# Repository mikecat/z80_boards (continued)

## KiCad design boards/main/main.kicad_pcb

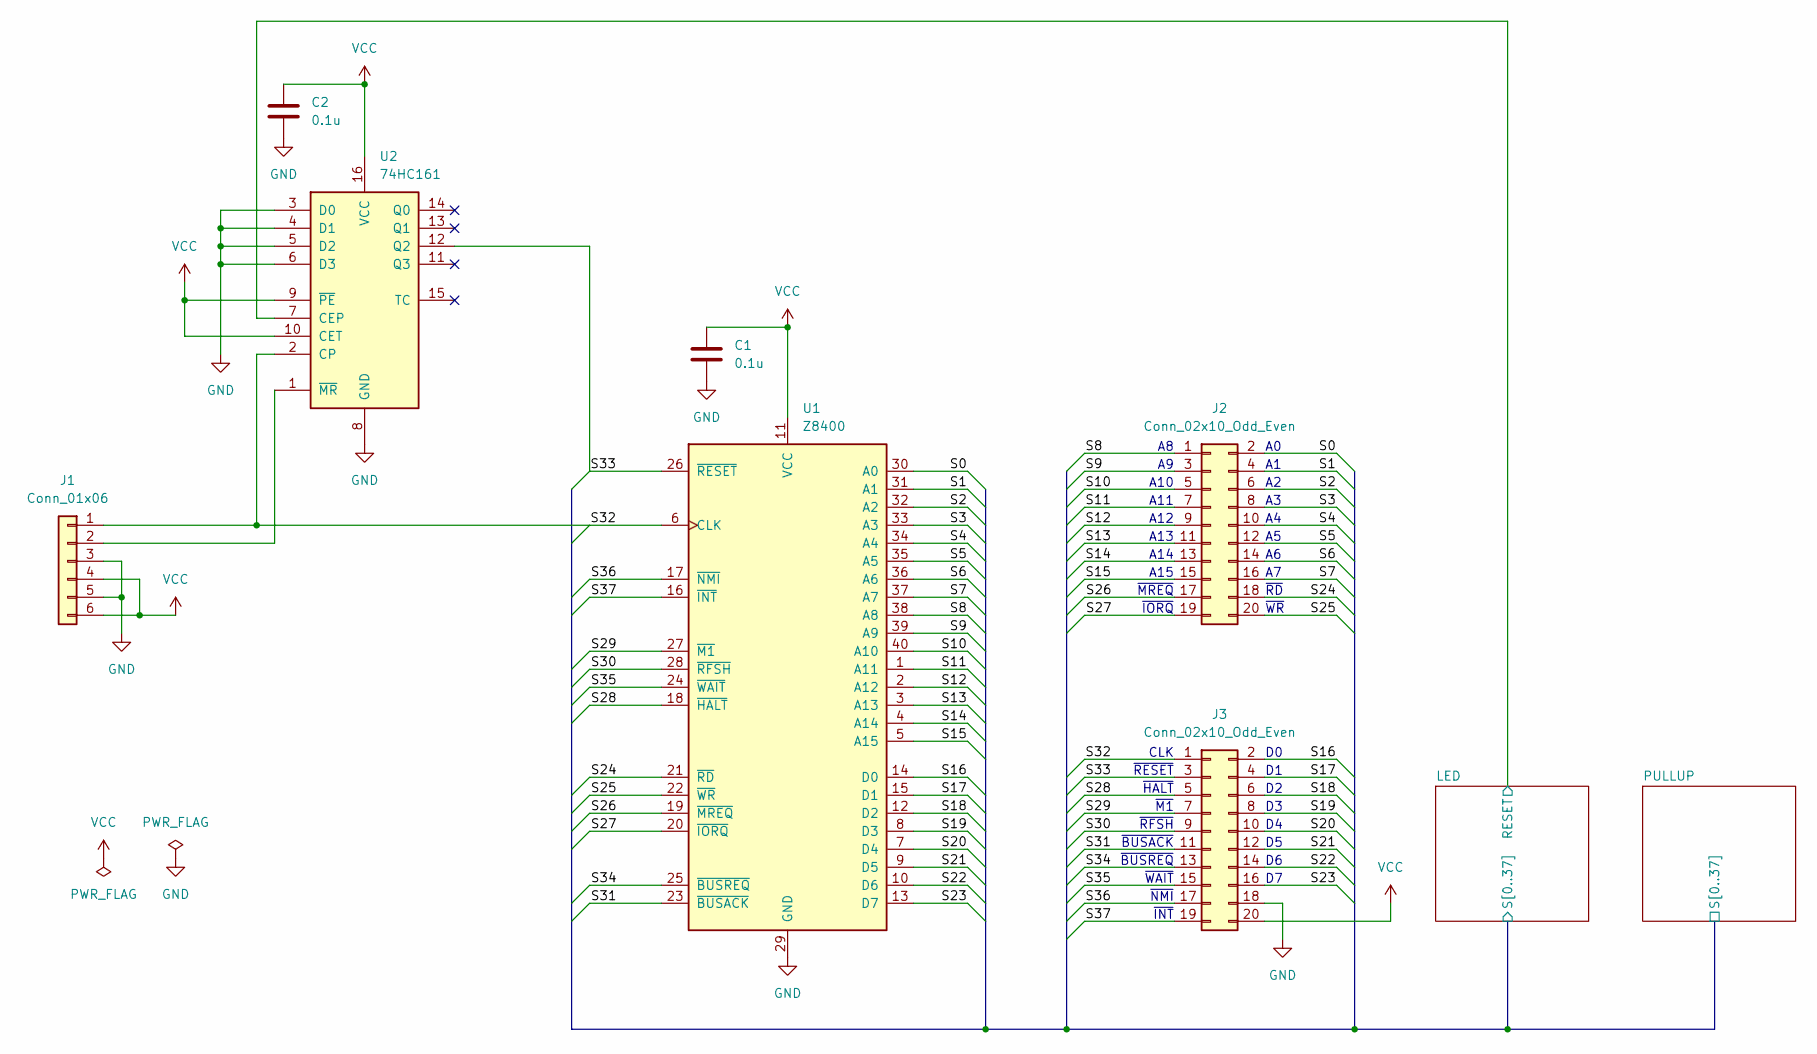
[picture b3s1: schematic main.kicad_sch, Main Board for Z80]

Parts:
C1, C2: 0.1u; C_0805_2012Metric_Pad1.18x1.45mm_HandSolder
J1: Conn_01x06; PinHeader_1x06_P2.54mm_Vertical
J2, J3: Conn_02x10_Odd_Even; PinHeader_2x10_P2.54mm_Vertical
U1: Z8400; DIP-40_W15.24mm
U2: 74HC161; DIP-16_W7.62mm

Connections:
/LED/S0: J2.2, U1.30 (A0); also elsewhere on the board
/LED/S1: J2.4, U1.31 (A1); also elsewhere on the board
/LED/S2: J2.6, U1.32 (A2); also elsewhere on the board
/LED/S3: J2.8, U1.33 (A3); also elsewhere on the board
/LED/S4: J2.10, U1.34 (A4); also elsewhere on the board
/LED/S5: J2.12, U1.35 (A5); also elsewhere on the board
/LED/S6: J2.14, U1.36 (A6); also elsewhere on the board
/LED/S7: J2.16, U1.37 (A7); also elsewhere on the board
/LED/S8: J2.1, U1.38 (A8); also elsewhere on the board
/LED/S9: J2.3, U1.39 (A9); also elsewhere on the board
/LED/S10: J2.5, U1.40 (A10); also elsewhere on the board
/LED/S11: J2.7, U1.1 (A11); also elsewhere on the board
/LED/S12: J2.9, U1.2 (A12); also elsewhere on the board
/LED/S13: J2.11, U1.3 (A13); also elsewhere on the board
/LED/S14: J2.13, U1.4 (A14); also elsewhere on the board
/LED/S15: J2.15, U1.5 (A15); also elsewhere on the board
/LED/S16: J3.2, U1.14 (D0); also elsewhere on the board
/LED/S17: J3.4, U1.15 (D1); also elsewhere on the board
/LED/S18: J3.6, U1.12 (D2); also elsewhere on the board
/LED/S19: J3.8, U1.8 (D3); also elsewhere on the board
/LED/S20: J3.10, U1.7 (D4); also elsewhere on the board
/LED/S21: J3.12, U1.9 (D5); also elsewhere on the board
/LED/S22: J3.14, U1.10 (D6); also elsewhere on the board
/LED/S23: J3.16, U1.13 (D7); also elsewhere on the board
/LED/S24: J2.18, U1.21 (~RD); also elsewhere on the board
/LED/S25: J2.20, U1.22 (~WR); also elsewhere on the board
/LED/S26: J2.17, U1.19 (~MREQ); also elsewhere on the board
/LED/S27: J2.19, U1.20 (~IORQ); also elsewhere on the board
/LED/S28: J3.5, U1.18 (~HALT); also elsewhere on the board
/LED/S29: J3.7, U1.27 (~M1); also elsewhere on the board
/LED/S30: J3.9, U1.28 (~RFSH); also elsewhere on the board
/LED/S31: J3.11, U1.23 (~BUSACK); also elsewhere on the board
/LED/S32: J1.1, J3.1, U1.6 (CLK), U2.2 (CP); also elsewhere on the board
/LED/S33: J3.3, U1.26 (~RESET), U2.12 (Q2); also elsewhere on the board
/LED/S34: J3.13, U1.25 (~BUSREQ); also elsewhere on the board
/LED/S35: J3.15, U1.24 (~WAIT); also elsewhere on the board
/LED/S36: J3.17, U1.17 (~NMI); also elsewhere on the board
/LED/S37: J3.19, U1.16 (~INT); also elsewhere on the board
/LED/~RESET_L: U2.7 (CEP); also elsewhere on the board
GND: C1.2, C2.2, J1.3, J1.5, J3.18, U1.29 (GND), U2.3 (D0), U2.4 (D1), U2.5 (D2), U2.6 (D3), U2.8 (GND); also elsewhere on the board
unnamed: J1.2, U2.1 (~MR)
VCC: C1.1, C2.1, J1.4, J1.6, J3.20, U1.11 (VCC), U2.9 (~PE), U2.10 (CET), U2.16 (VCC); also elsewhere on the board

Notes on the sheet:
~{WR}
~{INT}
~{RESET}
~{HALT}
~{RFSH}
~{BUSREQ}
A10
A13
A11
~{IORQ}
~{WAIT}
~{M1}
A14
CLK
~{NMI}
~{RD}
~{BUSACK}
A12
A15
~{MREQ}

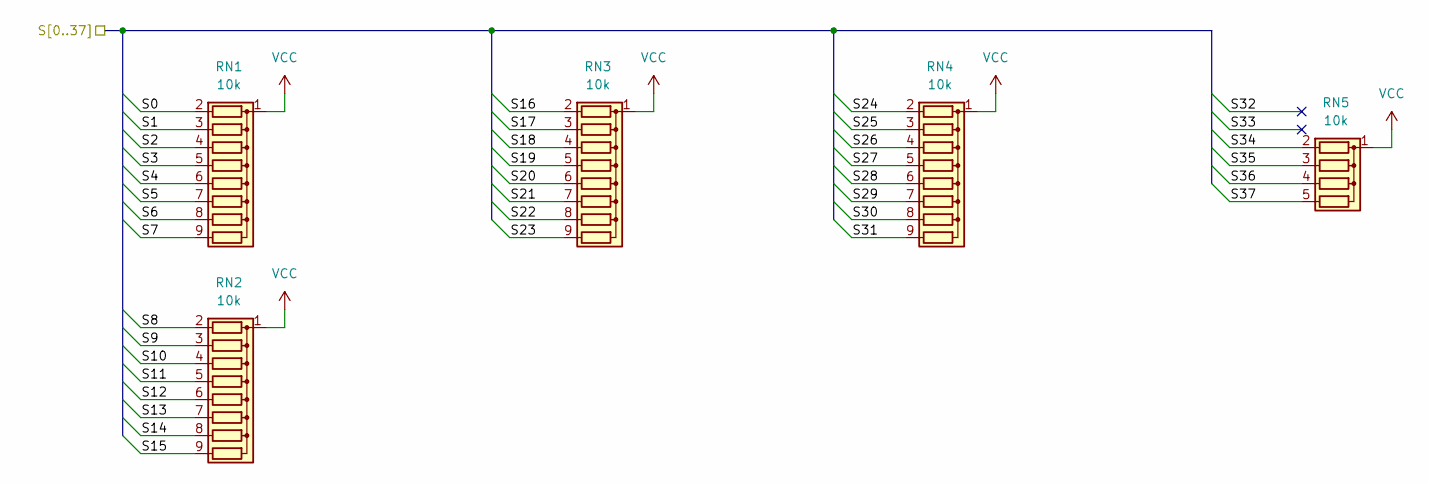
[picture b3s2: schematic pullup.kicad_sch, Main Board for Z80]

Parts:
RN1, RN2, RN3, RN4: 10k; R_Array_SIP9
RN5: 10k; R_Array_SIP5

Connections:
/LED/S0: RN1.2 (R1); also elsewhere on the board
/LED/S1: RN1.3 (R2); also elsewhere on the board
/LED/S2: RN1.4 (R3); also elsewhere on the board
/LED/S3: RN1.5 (R4); also elsewhere on the board
/LED/S4: RN1.6 (R5); also elsewhere on the board
/LED/S5: RN1.7 (R6); also elsewhere on the board
/LED/S6: RN1.8 (R7); also elsewhere on the board
/LED/S7: RN1.9 (R8); also elsewhere on the board
/LED/S8: RN2.2 (R1); also elsewhere on the board
/LED/S9: RN2.3 (R2); also elsewhere on the board
/LED/S10: RN2.4 (R3); also elsewhere on the board
/LED/S11: RN2.5 (R4); also elsewhere on the board
/LED/S12: RN2.6 (R5); also elsewhere on the board
/LED/S13: RN2.7 (R6); also elsewhere on the board
/LED/S14: RN2.8 (R7); also elsewhere on the board
/LED/S15: RN2.9 (R8); also elsewhere on the board
/LED/S16: RN3.2 (R1); also elsewhere on the board
/LED/S17: RN3.3 (R2); also elsewhere on the board
/LED/S18: RN3.4 (R3); also elsewhere on the board
/LED/S19: RN3.5 (R4); also elsewhere on the board
/LED/S20: RN3.6 (R5); also elsewhere on the board
/LED/S21: RN3.7 (R6); also elsewhere on the board
/LED/S22: RN3.8 (R7); also elsewhere on the board
/LED/S23: RN3.9 (R8); also elsewhere on the board
/LED/S24: RN4.2 (R1); also elsewhere on the board
/LED/S25: RN4.3 (R2); also elsewhere on the board
/LED/S26: RN4.4 (R3); also elsewhere on the board
/LED/S27: RN4.5 (R4); also elsewhere on the board
/LED/S28: RN4.6 (R5); also elsewhere on the board
/LED/S29: RN4.7 (R6); also elsewhere on the board
/LED/S30: RN4.8 (R7); also elsewhere on the board
/LED/S31: RN4.9 (R8); also elsewhere on the board
/LED/S34: RN5.2 (R1); also elsewhere on the board
/LED/S35: RN5.3 (R2); also elsewhere on the board
/LED/S36: RN5.4 (R3); also elsewhere on the board
/LED/S37: RN5.5 (R4); also elsewhere on the board
VCC: RN1.1 (common), RN2.1 (common), RN3.1 (common), RN4.1 (common), RN5.1 (common); also elsewhere on the board

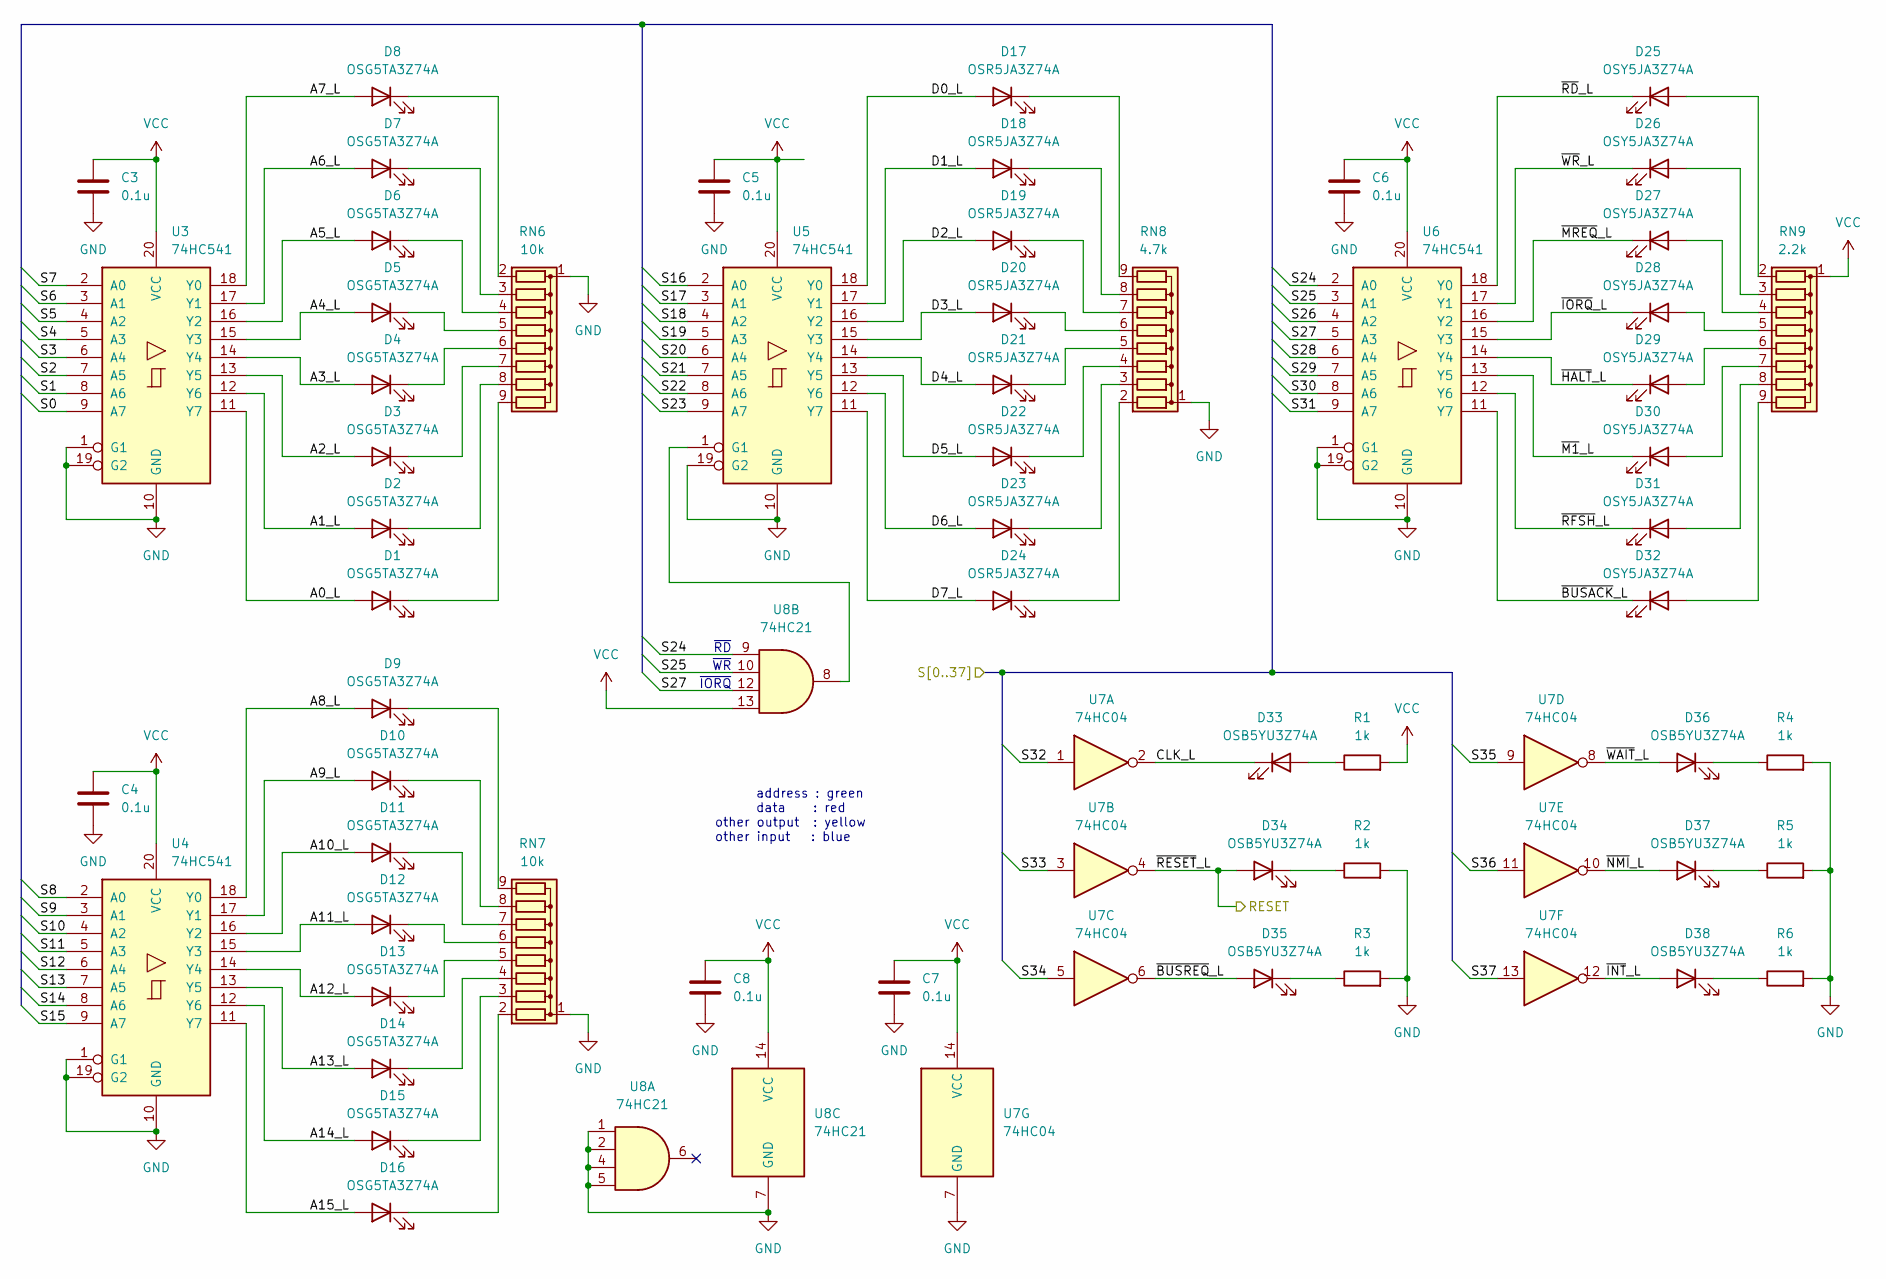
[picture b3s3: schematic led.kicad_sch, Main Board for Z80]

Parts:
C3, C4, C5, C6, C7, C8: 0.1u; C_0805_2012Metric_Pad1.18x1.45mm_HandSolder
D1, D2, D3, D4, D5, D6, D7, D8, D9, D10, D11, D12, D13, D14, D15, D16: OSG5TA3Z74A; LED_D3.0mm_Clear
D17, D18, D19, D20, D21, D22, D23, D24: OSR5JA3Z74A; LED_D3.0mm_Clear
D25, D26, D27, D28, D29, D30, D31, D32: OSY5JA3Z74A; LED_D3.0mm_Clear
D33, D34, D35, D36, D37, D38: OSB5YU3Z74A; LED_D3.0mm_Clear
R1, R2, R3, R4, R5, R6: 1k; R_0805_2012Metric_Pad1.20x1.40mm_HandSolder
RN6, RN7: 10k; R_Array_SIP9
RN8: 4.7k; R_Array_SIP9
RN9: 2.2k; R_Array_SIP9
U3, U4, U5, U6: 74HC541; DIP-20_W7.62mm
U7: 74HC04; DIP-14_W7.62mm
U8: 74HC21; DIP-14_W7.62mm

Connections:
/LED/A0_L: D1.2 (A), U3.11 (Y7)
/LED/A1_L: D2.2 (A), U3.12 (Y6)
/LED/A2_L: D3.2 (A), U3.13 (Y5)
/LED/A3_L: D4.2 (A), U3.14 (Y4)
/LED/A4_L: D5.2 (A), U3.15 (Y3)
/LED/A5_L: D6.2 (A), U3.16 (Y2)
/LED/A6_L: D7.2 (A), U3.17 (Y1)
/LED/A7_L: D8.2 (A), U3.18 (Y0)
/LED/A8_L: D9.2 (A), U4.18 (Y0)
/LED/A9_L: D10.2 (A), U4.17 (Y1)
/LED/A10_L: D11.2 (A), U4.16 (Y2)
/LED/A11_L: D12.2 (A), U4.15 (Y3)
/LED/A12_L: D13.2 (A), U4.14 (Y4)
/LED/A13_L: D14.2 (A), U4.13 (Y5)
/LED/A14_L: D15.2 (A), U4.12 (Y6)
/LED/A15_L: D16.2 (A), U4.11 (Y7)
/LED/CLK_L: D33.1 (K), U7.2
/LED/D0_L: D17.2 (A), U5.18 (Y0)
/LED/D1_L: D18.2 (A), U5.17 (Y1)
/LED/D2_L: D19.2 (A), U5.16 (Y2)
/LED/D3_L: D20.2 (A), U5.15 (Y3)
/LED/D4_L: D21.2 (A), U5.14 (Y4)
/LED/D5_L: D22.2 (A), U5.13 (Y5)
/LED/D6_L: D23.2 (A), U5.12 (Y6)
/LED/D7_L: D24.2 (A), U5.11 (Y7)
/LED/S0: U3.9 (A7); also elsewhere on the board
/LED/S1: U3.8 (A6); also elsewhere on the board
/LED/S2: U3.7 (A5); also elsewhere on the board
/LED/S3: U3.6 (A4); also elsewhere on the board
/LED/S4: U3.5 (A3); also elsewhere on the board
/LED/S5: U3.4 (A2); also elsewhere on the board
/LED/S6: U3.3 (A1); also elsewhere on the board
/LED/S7: U3.2 (A0); also elsewhere on the board
/LED/S8: U4.2 (A0); also elsewhere on the board
/LED/S9: U4.3 (A1); also elsewhere on the board
/LED/S10: U4.4 (A2); also elsewhere on the board
/LED/S11: U4.5 (A3); also elsewhere on the board
/LED/S12: U4.6 (A4); also elsewhere on the board
/LED/S13: U4.7 (A5); also elsewhere on the board
/LED/S14: U4.8 (A6); also elsewhere on the board
/LED/S15: U4.9 (A7); also elsewhere on the board
/LED/S16: U5.2 (A0); also elsewhere on the board
/LED/S17: U5.3 (A1); also elsewhere on the board
/LED/S18: U5.4 (A2); also elsewhere on the board
/LED/S19: U5.5 (A3); also elsewhere on the board
/LED/S20: U5.6 (A4); also elsewhere on the board
/LED/S21: U5.7 (A5); also elsewhere on the board
/LED/S22: U5.8 (A6); also elsewhere on the board
/LED/S23: U5.9 (A7); also elsewhere on the board
/LED/S24: U6.2 (A0), U8.9; also elsewhere on the board
/LED/S25: U6.3 (A1), U8.10; also elsewhere on the board
/LED/S26: U6.4 (A2); also elsewhere on the board
/LED/S27: U6.5 (A3), U8.12; also elsewhere on the board
/LED/S28: U6.6 (A4); also elsewhere on the board
/LED/S29: U6.7 (A5); also elsewhere on the board
/LED/S30: U6.8 (A6); also elsewhere on the board
/LED/S31: U6.9 (A7); also elsewhere on the board
/LED/S32: U7.1; also elsewhere on the board
/LED/S33: U7.3; also elsewhere on the board
/LED/S34: U7.5; also elsewhere on the board
/LED/S35: U7.9; also elsewhere on the board
/LED/S36: U7.11; also elsewhere on the board
/LED/S37: U7.13; also elsewhere on the board
/LED/~BUSACK_L: D32.1 (K), U6.11 (Y7)
/LED/~BUSREQ_L: D35.2 (A), U7.6
/LED/~HALT_L: D29.1 (K), U6.14 (Y4)
/LED/~INT_L: D38.2 (A), U7.12
/LED/~IORQ_L: D28.1 (K), U6.15 (Y3)
/LED/~M1_L: D30.1 (K), U6.13 (Y5)
/LED/~MREQ_L: D27.1 (K), U6.16 (Y2)
/LED/~NMI_L: D37.2 (A), U7.10
/LED/~RD_L: D25.1 (K), U6.18 (Y0)
/LED/~RESET_L: D34.2 (A), U7.4; also elsewhere on the board
/LED/~RFSH_L: D31.1 (K), U6.12 (Y6)
/LED/~WAIT_L: D36.2 (A), U7.8
/LED/~WR_L: D26.1 (K), U6.17 (Y1)
GND: C3.2, C4.2, C5.2, C6.2, C7.2, C8.2, R2.2, R3.2, R4.2, R5.2, R6.2, RN6.1 (common), RN7.1 (common), RN8.1 (common), U3.1 (G1), U3.10 (GND), U3.19 (G2), U4.1 (G1), U4.10 (GND), U4.19 (G2), U5.10 (GND), U5.19 (G2), U6.1 (G1), U6.10 (GND), U6.19 (G2), U7.7 (GND), U8.1, U8.2, U8.4, U8.5, U8.7 (GND); also elsewhere on the board
unnamed: D1.1 (K), RN6.9 (R8)
unnamed: D2.1 (K), RN6.8 (R7)
unnamed: D3.1 (K), RN6.7 (R6)
unnamed: D4.1 (K), RN6.6 (R5)
unnamed: D5.1 (K), RN6.5 (R4)
unnamed: D6.1 (K), RN6.4 (R3)
unnamed: D7.1 (K), RN6.3 (R2)
unnamed: D8.1 (K), RN6.2 (R1)
unnamed: D9.1 (K), RN7.9 (R8)
unnamed: D10.1 (K), RN7.8 (R7)
unnamed: D11.1 (K), RN7.7 (R6)
unnamed: D12.1 (K), RN7.6 (R5)
unnamed: D13.1 (K), RN7.5 (R4)
unnamed: D14.1 (K), RN7.4 (R3)
unnamed: D15.1 (K), RN7.3 (R2)
unnamed: D16.1 (K), RN7.2 (R1)
unnamed: D17.1 (K), RN8.9 (R8)
unnamed: D18.1 (K), RN8.8 (R7)
unnamed: D19.1 (K), RN8.7 (R6)
unnamed: D20.1 (K), RN8.6 (R5)
unnamed: D21.1 (K), RN8.5 (R4)
unnamed: D22.1 (K), RN8.4 (R3)
unnamed: D23.1 (K), RN8.3 (R2)
unnamed: D24.1 (K), RN8.2 (R1)
unnamed: D25.2 (A), RN9.2 (R1)
unnamed: D26.2 (A), RN9.3 (R2)
unnamed: D27.2 (A), RN9.4 (R3)
unnamed: D28.2 (A), RN9.5 (R4)
unnamed: D29.2 (A), RN9.6 (R5)
unnamed: D30.2 (A), RN9.7 (R6)
unnamed: D31.2 (A), RN9.8 (R7)
unnamed: D32.2 (A), RN9.9 (R8)
unnamed: D33.2 (A), R1.1
unnamed: D34.1 (K), R2.1
unnamed: D35.1 (K), R3.1
unnamed: D36.1 (K), R4.1
unnamed: D37.1 (K), R5.1
unnamed: D38.1 (K), R6.1
unnamed: U5.1 (G1), U8.8
VCC: C3.1, C4.1, C5.1, C6.1, C7.1, C8.1, R1.2, RN9.1 (common), U3.20 (VCC), U4.20 (VCC), U5.20 (VCC), U6.20 (VCC), U7.14 (VCC), U8.13, U8.14 (VCC); also elsewhere on the board

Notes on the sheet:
address : green data : red other output : yellow other input : blue
~{WR}
~{IORQ}
~{RD}

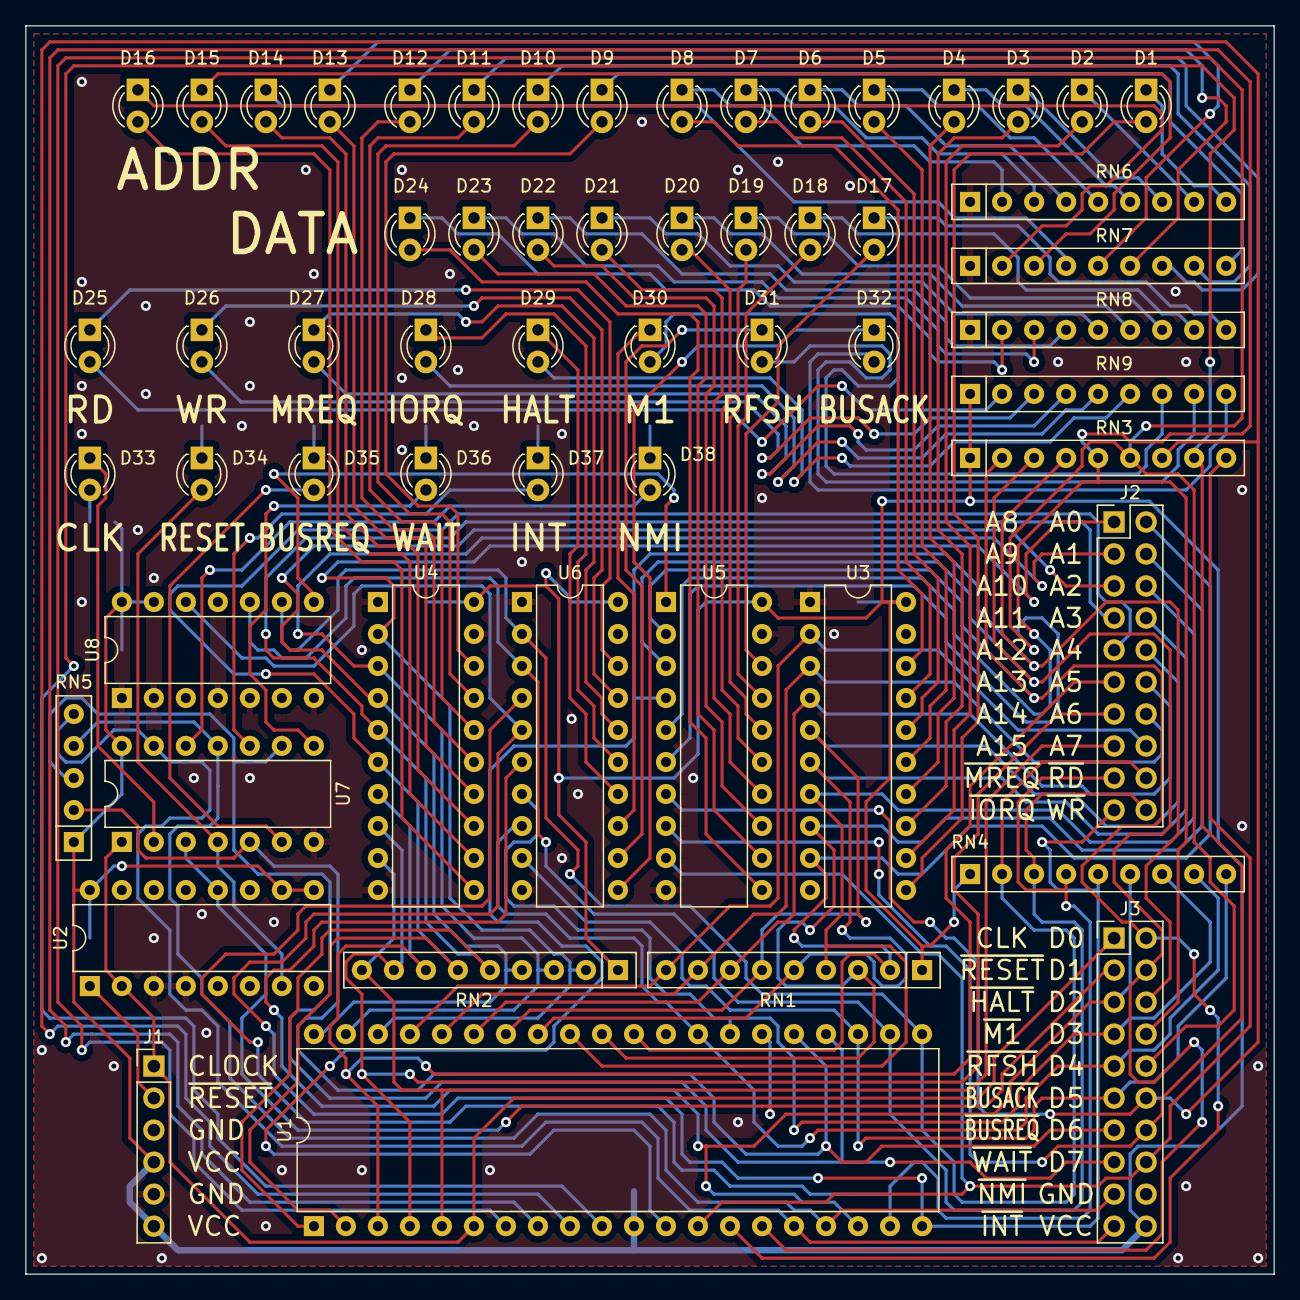
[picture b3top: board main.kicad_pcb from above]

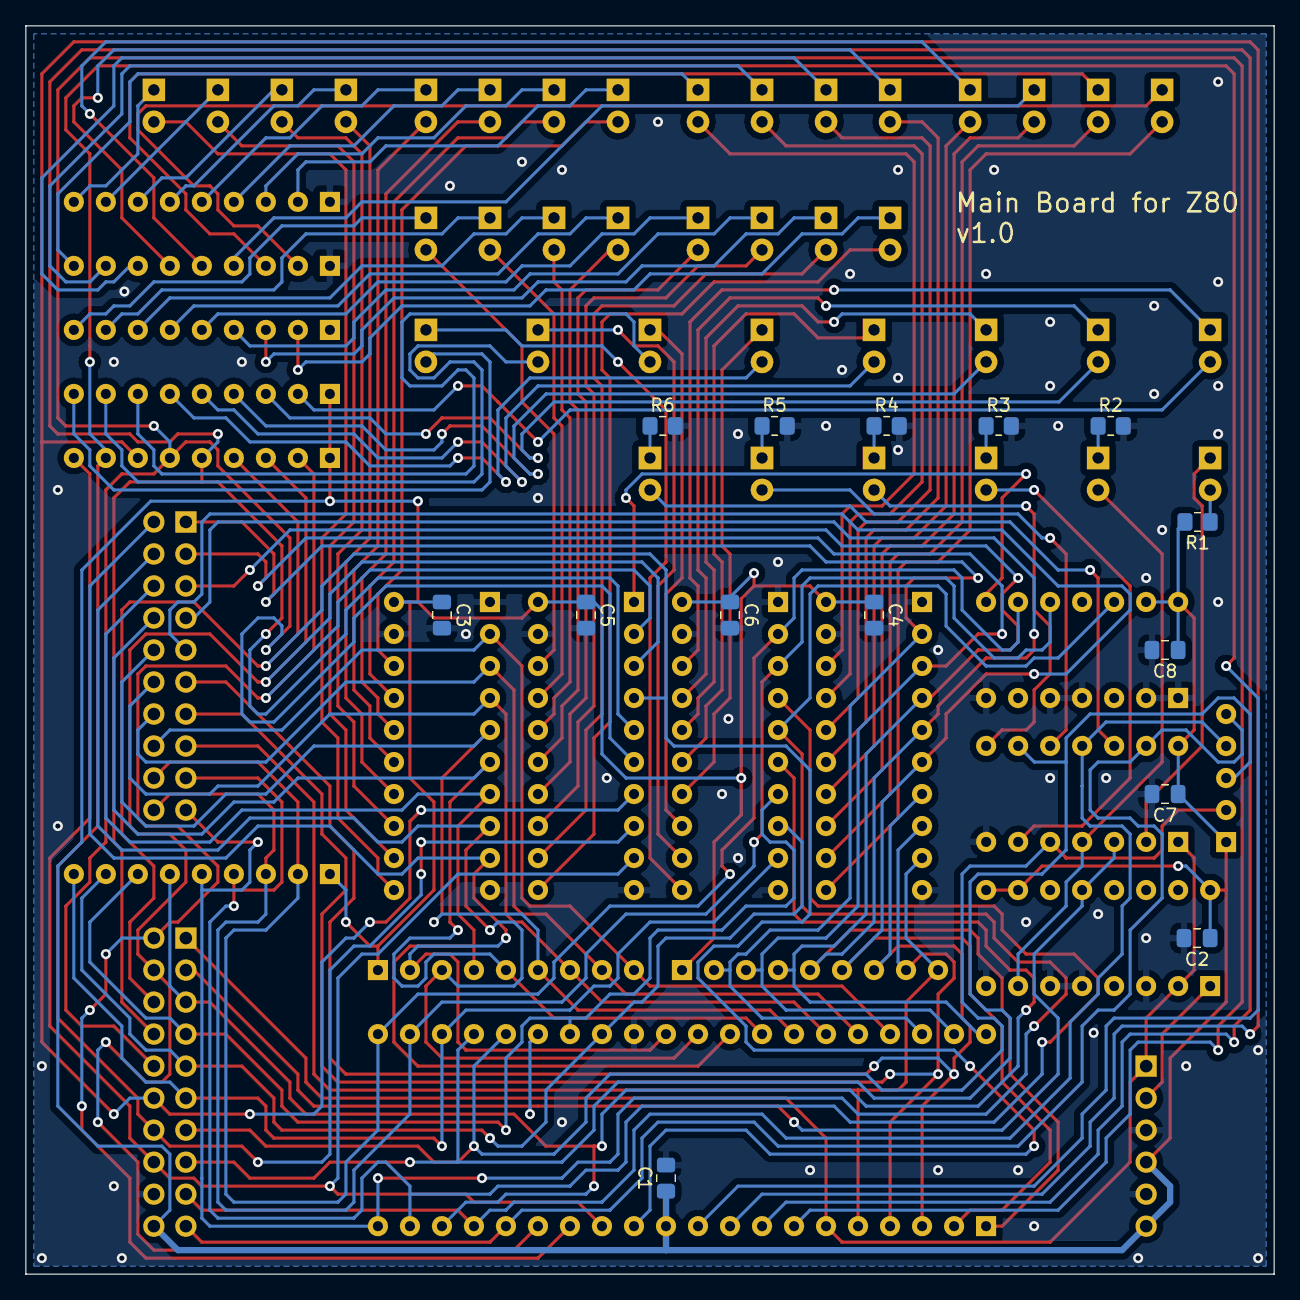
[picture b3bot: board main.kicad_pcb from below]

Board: 2 copper layers, 99.1 x 99.1 mm, 72 parts (14 on the bottom side), 118 nets.

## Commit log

2023-02-02 add main board
2023-02-03 add board memory256x2
2023-02-08 add gpio board
